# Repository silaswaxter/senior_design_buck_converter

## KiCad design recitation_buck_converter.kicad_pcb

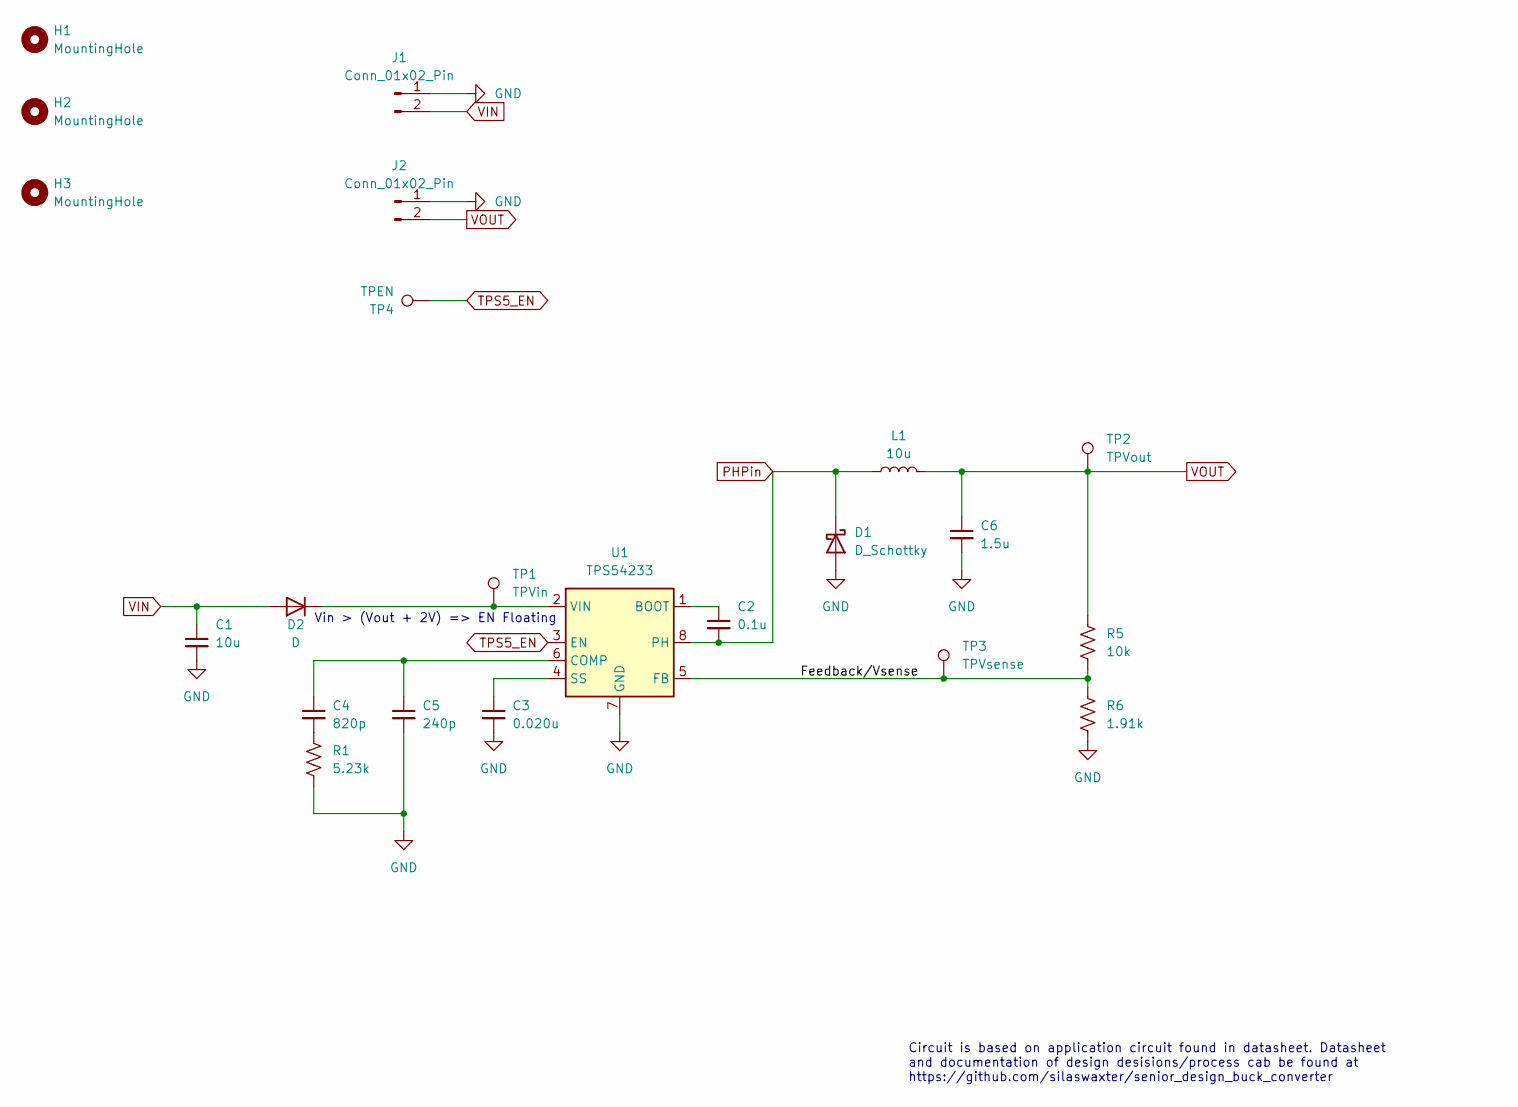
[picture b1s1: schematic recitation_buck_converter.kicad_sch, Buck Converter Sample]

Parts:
C1: 10u; C_0805_2012Metric_Pad1.18x1.45mm_HandSolder; Digikey PN 399-11939-2-ND
C2: 0.1u; C_0805_2012Metric_Pad1.18x1.45mm_HandSolder; Digikey PN 399-C0805C104M5RAC7800CT-ND
C3: 0.020u; C_0805_2012Metric_Pad1.18x1.45mm_HandSolder; Digikey PN 478-08055C203KAT2ATR-ND
C4: 820p; C_0805_2012Metric_Pad1.18x1.45mm_HandSolder; Digikey PN 311-3382-1-ND
C5: 240p; C_0805_2012Metric_Pad1.18x1.45mm_HandSolder; Digikey PN 311-4232-1-ND
C6: 1.5u; C_0805_2012Metric_Pad1.18x1.45mm_HandSolder; Digikey PN 732-7655-2-ND
D1: D_Schottky; US2H; Digikey PN CUHS20F30H3FTR-ND
D2: D; D_SMA; Digikey PN 2616-SK26A-ND
H1, H2, H3: MountingHole; MountingHole_2.2mm_M2; Digikey PN DNP
J1, J2: Conn_01x02_Pin; JST_XH_B2B-XH-AM_1x02_P2.50mm_Vertical; Digikey PN DNP
L1: 10u; L_Axial_L9.5mm_D4.0mm_P5.08mm_Vertical_Fastron_SMCC; Digikey PN 495-6962-1-ND
R1: 5.23k; R_0805_2012Metric_Pad1.20x1.40mm_HandSolder; Digikey PN 311-5.23KCRCT-ND
R5: 10k; R_0805_2012Metric; Digikey PN RMCF0805FT10K0TR-ND
R6: 1.91k; R_0805_2012Metric_Pad1.20x1.40mm_HandSolder; Digikey PN 311-1.91KCRTR-ND
TP1: TPVin; TestPoint_Pad_1.5x1.5mm
TP2: TPVout; TestPoint_Pad_1.5x1.5mm
TP3: TPVsense; TestPoint_Pad_1.5x1.5mm
TP4: TPEN; TestPoint_Pad_1.5x1.5mm
U1: TPS54233; SOIC-8_3.9x4.9mm_P1.27mm; Digikey PN 296-23902-1-ND

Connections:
/Feedback/Vsense: R5.2, R6.1, TP3.1, U1.5 (FB)
GND: C1.2, C3.2, C5.2, C6.2, D1.2 (A), J1.1, J2.1, R1.2, R6.2, U1.7 (GND)
unnamed: C4.2, R1.1
unnamed: D2.1 (K), TP1.1, U1.2 (VIN)
unnamed: C2.1, U1.1 (BOOT)
unnamed: C4.1, C5.1, U1.6 (COMP)
unnamed: C3.1, U1.4 (SS)
PHPin: C2.2, D1.1 (K), L1.1, U1.8 (PH)
TPS5_EN: TP4.1, U1.3 (EN)
VIN: C1.1, D2.2 (A), J1.2
VOUT: C6.1, J2.2, L1.2, R5.1, TP2.1

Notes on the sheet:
Vin > (Vout + 2V) => EN Floating
Circuit is based on application circuit found in datasheet. Datasheet and documentation of design desisions/process cab be found at https://github.com/silaswaxter/senior_design_buck_converter

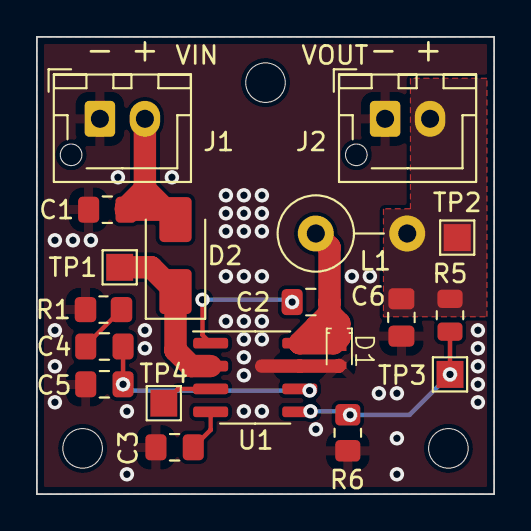
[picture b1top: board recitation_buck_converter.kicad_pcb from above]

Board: 2 copper layers, 25.4 x 25.4 mm, 22 parts (0 on the bottom side), 11 nets.

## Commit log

2023-10-05 chore: add kicad git ignore
2023-10-05 docs: clone converter requirements
2023-10-05 chore(datasheets): add datasheet for TI buck converter chip
2023-10-05 chore(gitignore): untrack lck and autosave files
2023-10-05 feat(schematic): minimal work for recitation 1 checkoff
2023-10-09 wip(design_decisions): read and document details from datasheet
2023-10-13 feat: update components to match specs and start layout
2023-10-13 docs(design): describe process for selecting vout resistors and inductor
2023-10-25 feat: add output components, float EN, and layouu with good track width
2023-11-02 feat: add compensation network; finish pcb
2023-11-02 fix(pcb): move dimensions to drawing layer
2023-11-02 feat: add vias for front-back ground fill
2023-11-02 chore(gitignore): don't track gerbers or week 5 submission
